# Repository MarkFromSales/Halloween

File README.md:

# Halloween
Various components associated with my Halloween decorations

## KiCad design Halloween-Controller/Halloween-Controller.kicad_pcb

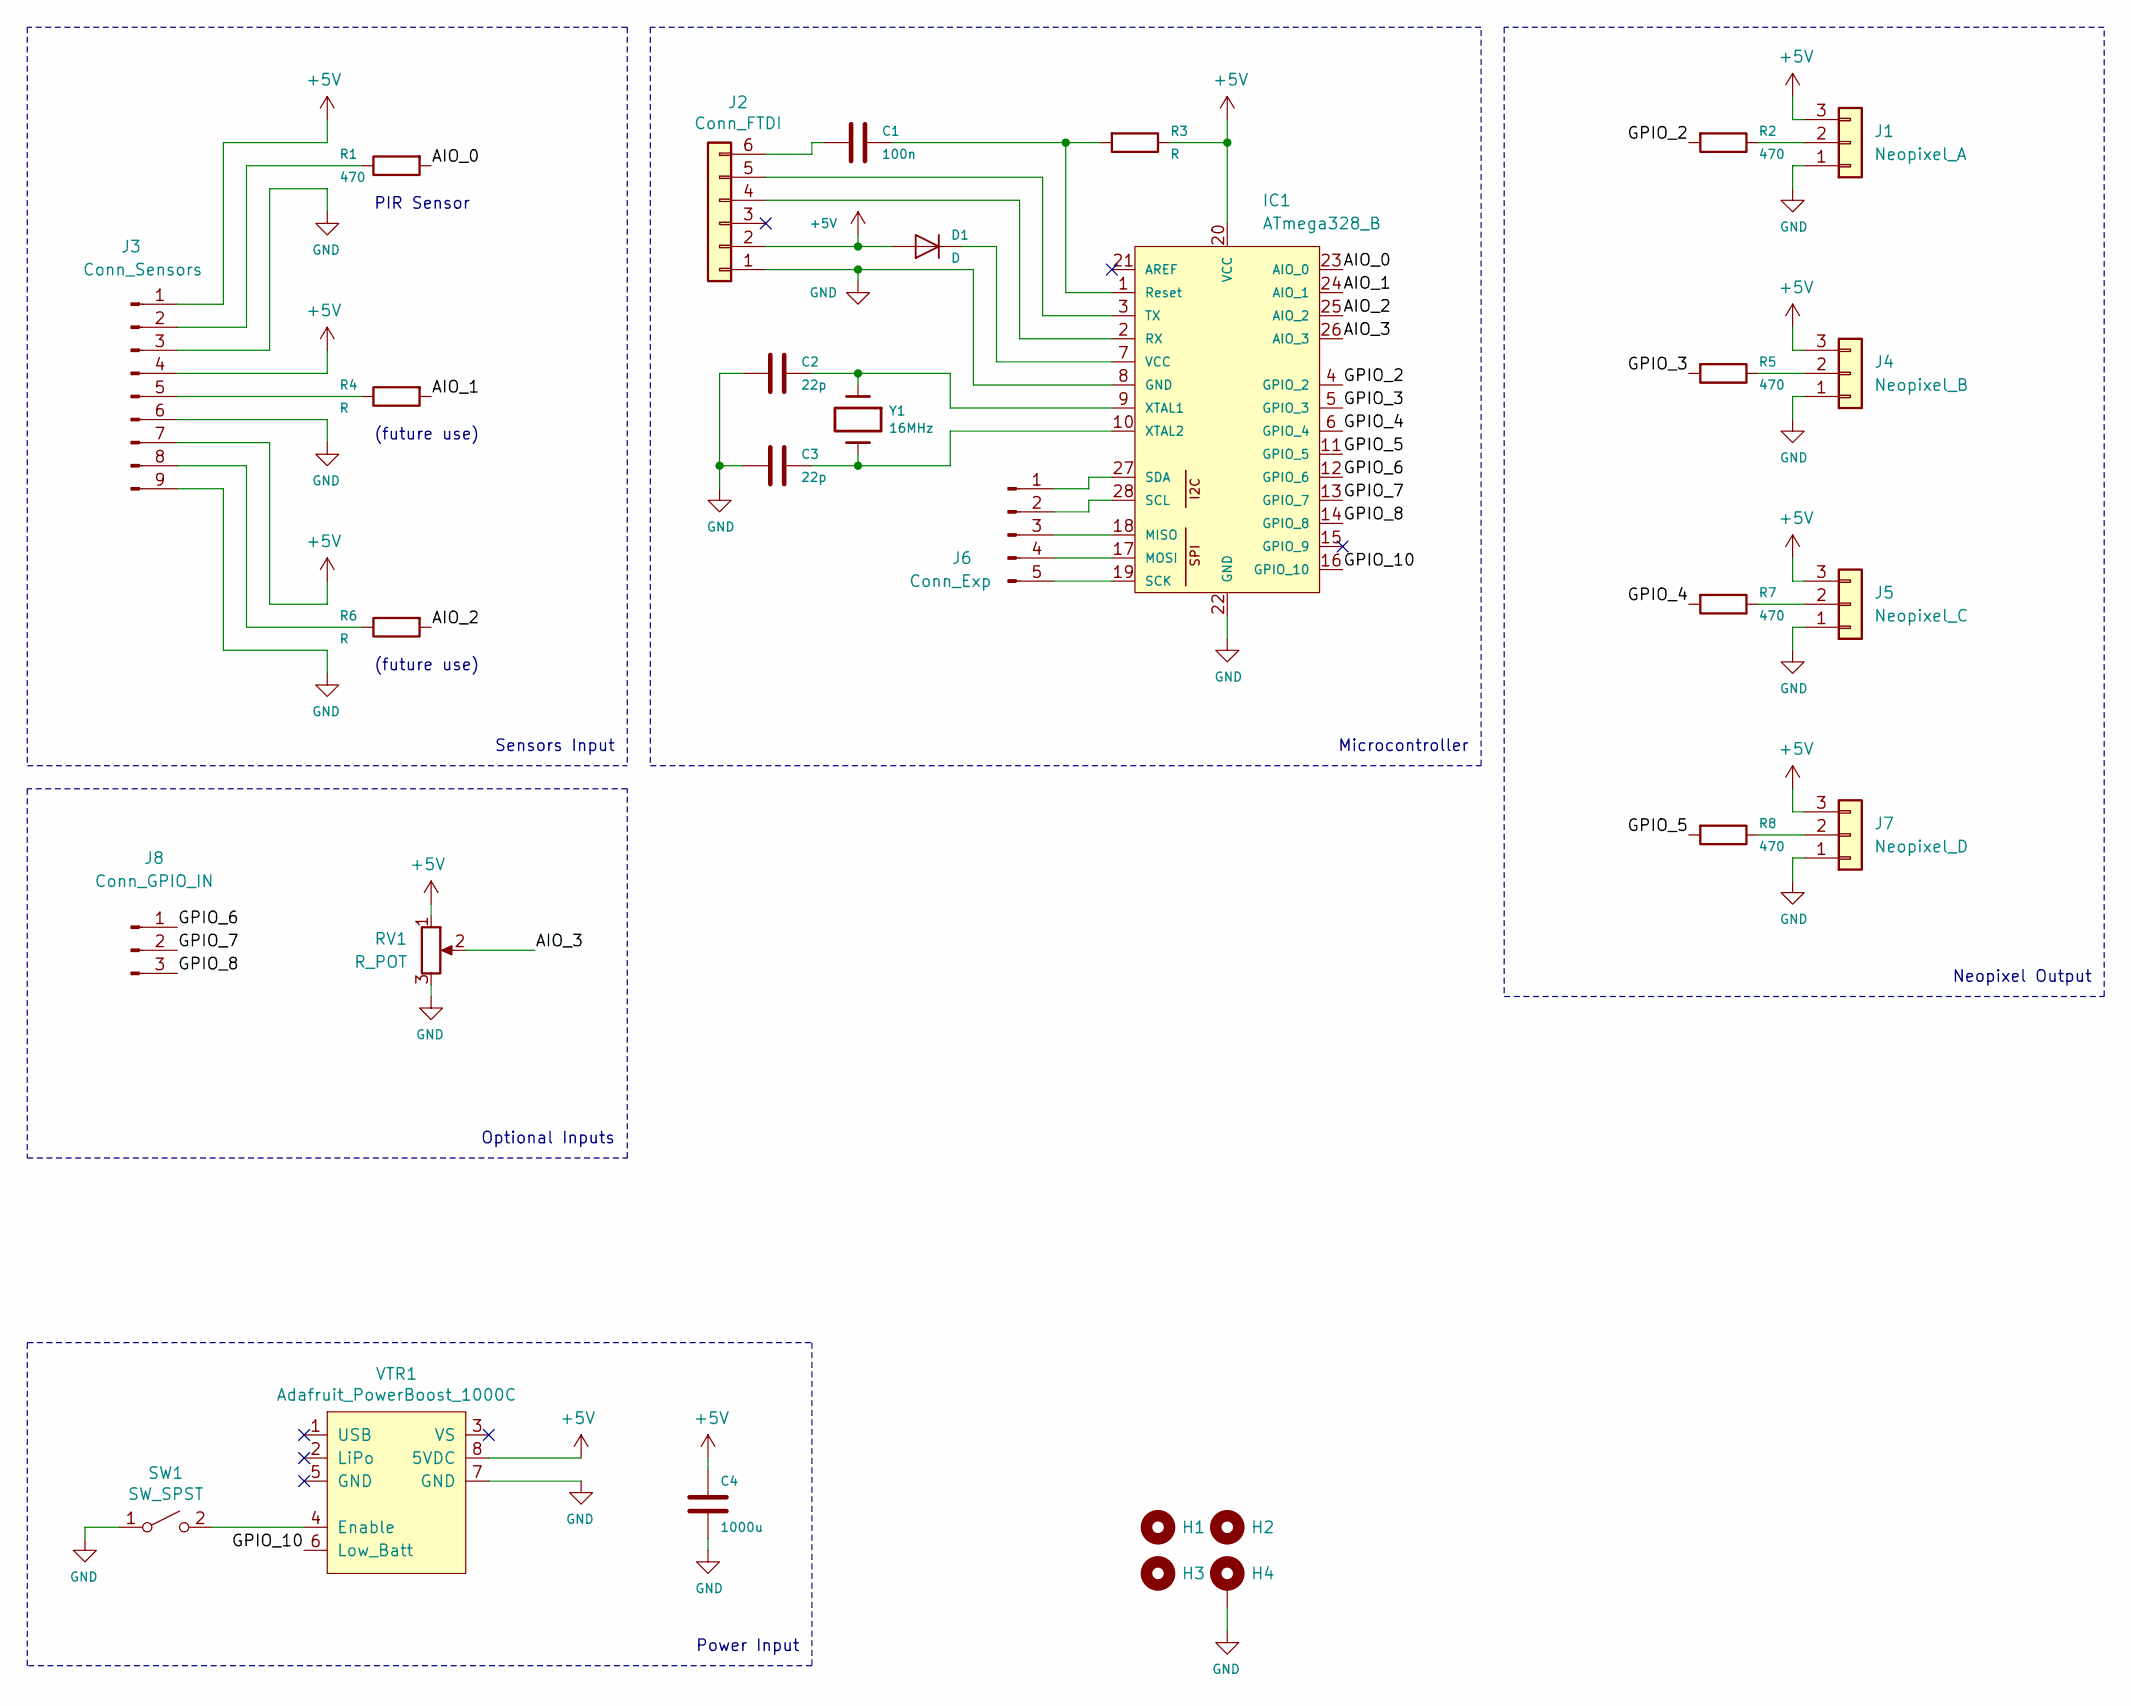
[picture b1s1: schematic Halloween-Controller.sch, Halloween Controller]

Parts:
C1: 100n; C_Disc_D10.5mm_W5.0mm_P7.50mm
C2, C3: 22p; C_0805_2012Metric_Pad1.15x1.40mm_HandSolder
C4: 1000u; C_1206_3216Metric_Pad1.42x1.75mm_HandSolder
D1: D; D_0805_2012Metric_Pad1.15x1.40mm_HandSolder
H1, H2, H3: MountingHole; MountingHole_3.2mm_M3
H4: MountingHole; MountingHole_3.2mm_M3_Pad
IC1: ATmega328_B; DIP-28_W7.62mm_Socket
J1: Neopixel_A; JST_XH_B03B-XH-A_1x03_P2.50mm_Vertical
J2: Conn_FTDI; PinHeader_1x06_P2.54mm_Vertical
J3: Conn_Sensors; PinHeader_1x09_P2.54mm_Vertical
J4: Neopixel_B; JST_XH_B03B-XH-A_1x03_P2.50mm_Vertical
J5: Neopixel_C; JST_XH_B03B-XH-A_1x03_P2.50mm_Vertical
J6: Conn_Exp; PinHeader_1x05_P2.54mm_Vertical
J7: Neopixel_D; JST_XH_B03B-XH-A_1x03_P2.50mm_Vertical
J8: Conn_GPIO_IN; PinHeader_1x03_P2.54mm_Vertical
R1, R2, R5, R7, R8: 470; R_0805_2012Metric
R3, R4, R6: R; R_0805_2012Metric
RV1: R_POT; Potentiometer
SW1: SW_SPST; PinHeader_1x02_P2.54mm_Vertical
VTR1: Adafruit_PowerBoost_1000C; PinHeader_1x08_P2.54mm_Vertical
Y1: 16MHz; Crystal_HC49-U_Vertical

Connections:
+5V: C4.1, D1.2 (A), IC1.20 (VCC), J1.3, J2.2, J3.1, J3.4, J3.7, J4.3, J5.3, J7.3, R3.1, RV1.1, VTR1.8 (5VDC)
/AIO_0: IC1.23 (AIO_0), R1.2
/AIO_1: IC1.24 (AIO_1), R4.2
/AIO_2: IC1.25 (AIO_2), R6.2
/AIO_3: IC1.26 (AIO_3), RV1.2
/GPIO_2: IC1.4 (GPIO_2), R2.2
/GPIO_3: IC1.5 (GPIO_3), R5.2
/GPIO_4: IC1.6 (GPIO_4), R7.2
/GPIO_5: IC1.11 (GPIO_5), R8.2
/GPIO_6: IC1.12 (GPIO_6), J8.1
/GPIO_7: IC1.13 (GPIO_7), J8.2
/GPIO_8: IC1.14 (GPIO_8), J8.3
/GPIO_10: IC1.16 (GPIO_10), VTR1.6 (Low_Batt)
GND: C2.2, C3.2, C4.2, H4.1, IC1.8 (GND), IC1.22 (GND), J1.1, J2.1, J3.3, J3.6, J3.9, J4.1, J5.1, J7.1, RV1.3, SW1.1 (A), VTR1.7 (GND)
unnamed: C1.1, IC1.1 (Reset), R3.2
unnamed: C1.2, J2.6
unnamed: C2.1, IC1.9 (XTAL1), Y1.1
unnamed: C3.1, IC1.10 (XTAL2), Y1.2
unnamed: D1.1 (K), IC1.7 (VCC)
unnamed: IC1.2 (RX), J2.4
unnamed: IC1.3 (TX), J2.5
unnamed: IC1.17 (MOSI), J6.4
unnamed: IC1.18 (MISO), J6.3
unnamed: IC1.19 (SCK), J6.5
unnamed: IC1.27 (SDA), J6.1
unnamed: IC1.28 (SCL), J6.2
unnamed: J1.2, R2.1
unnamed: J3.2, R1.1
unnamed: J3.5, R4.1
unnamed: J3.8, R6.1
unnamed: J4.2, R5.1
unnamed: J5.2, R7.1
unnamed: J7.2, R8.1
unnamed: SW1.2 (B), VTR1.4 (Enable)

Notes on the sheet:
PIR Sensor
(future use)
Sensors Input
Neopixel Output
Optional Inputs
Power Input
Microcontroller

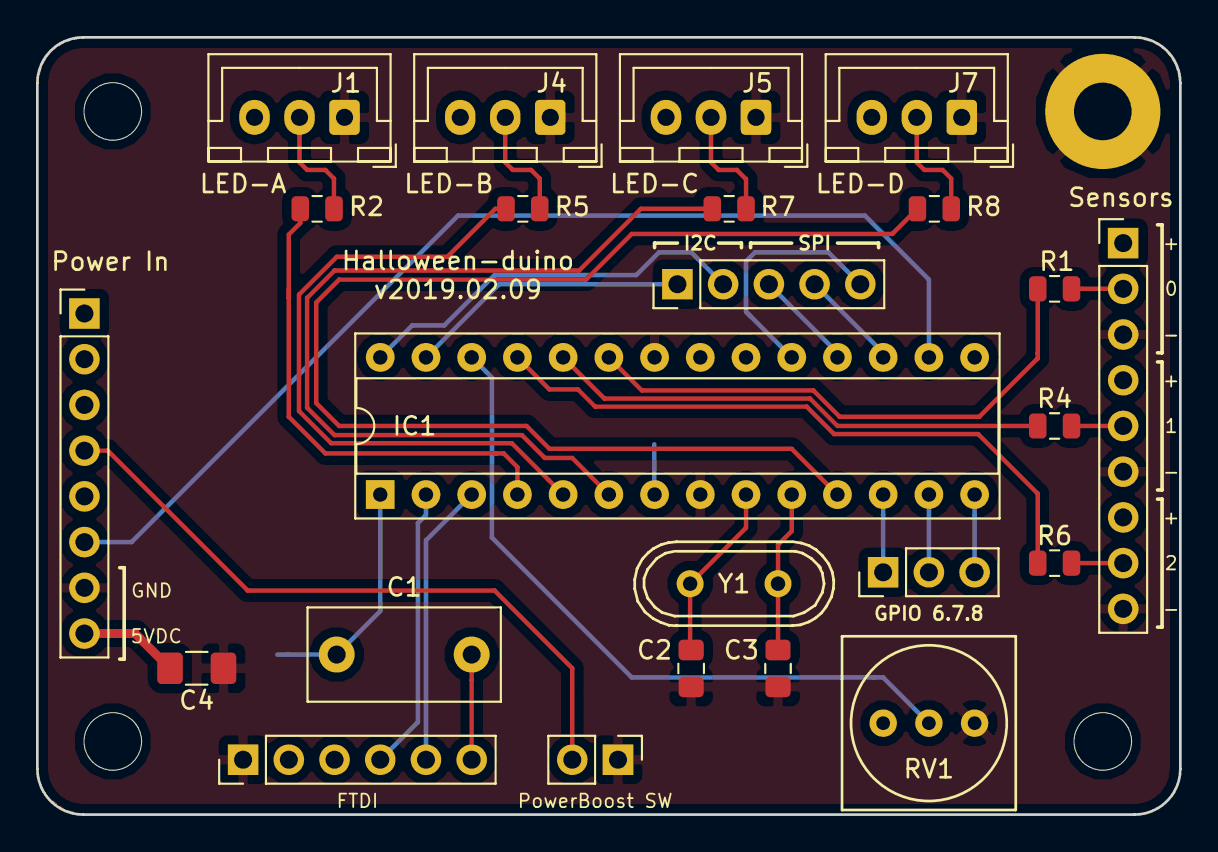
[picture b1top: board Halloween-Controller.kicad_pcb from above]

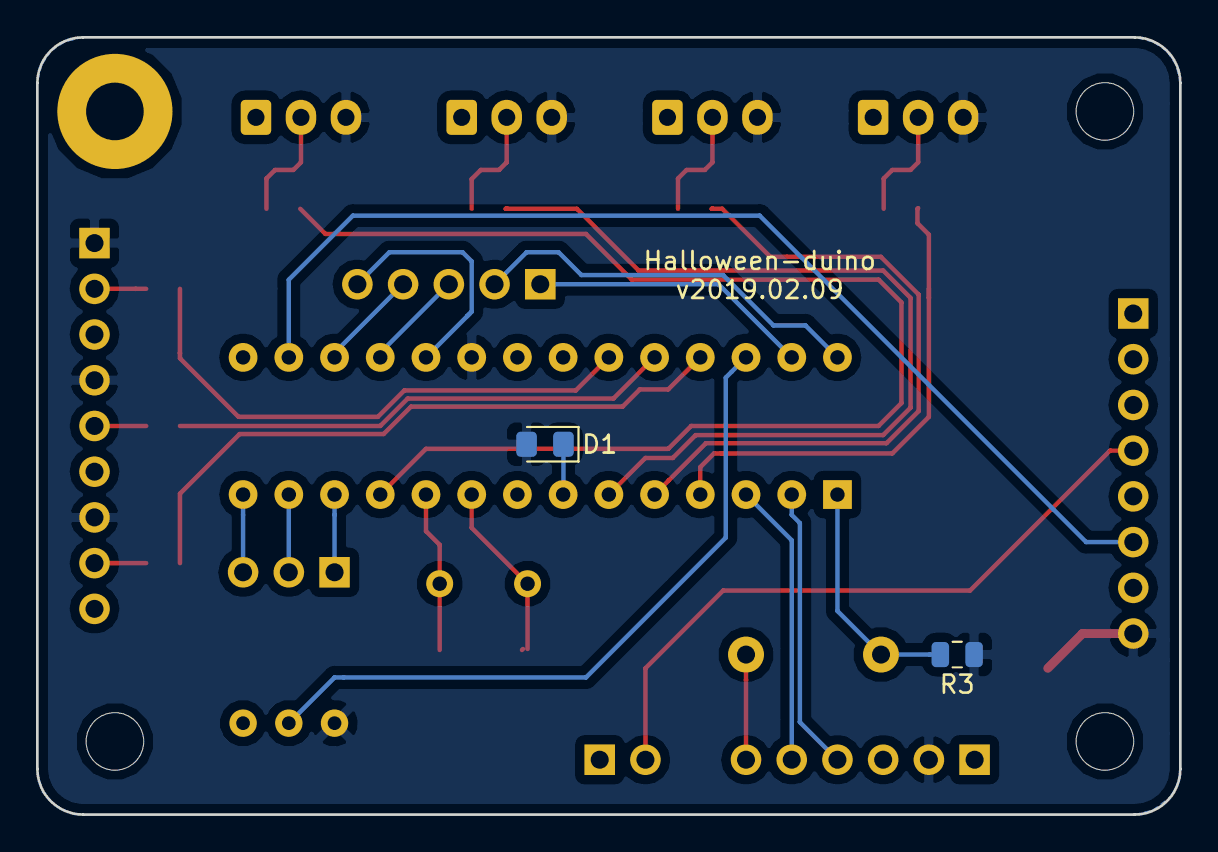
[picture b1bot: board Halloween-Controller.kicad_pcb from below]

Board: 2 copper layers, 63.5 x 43.2 mm, 30 parts (2 on the bottom side), 34 nets.

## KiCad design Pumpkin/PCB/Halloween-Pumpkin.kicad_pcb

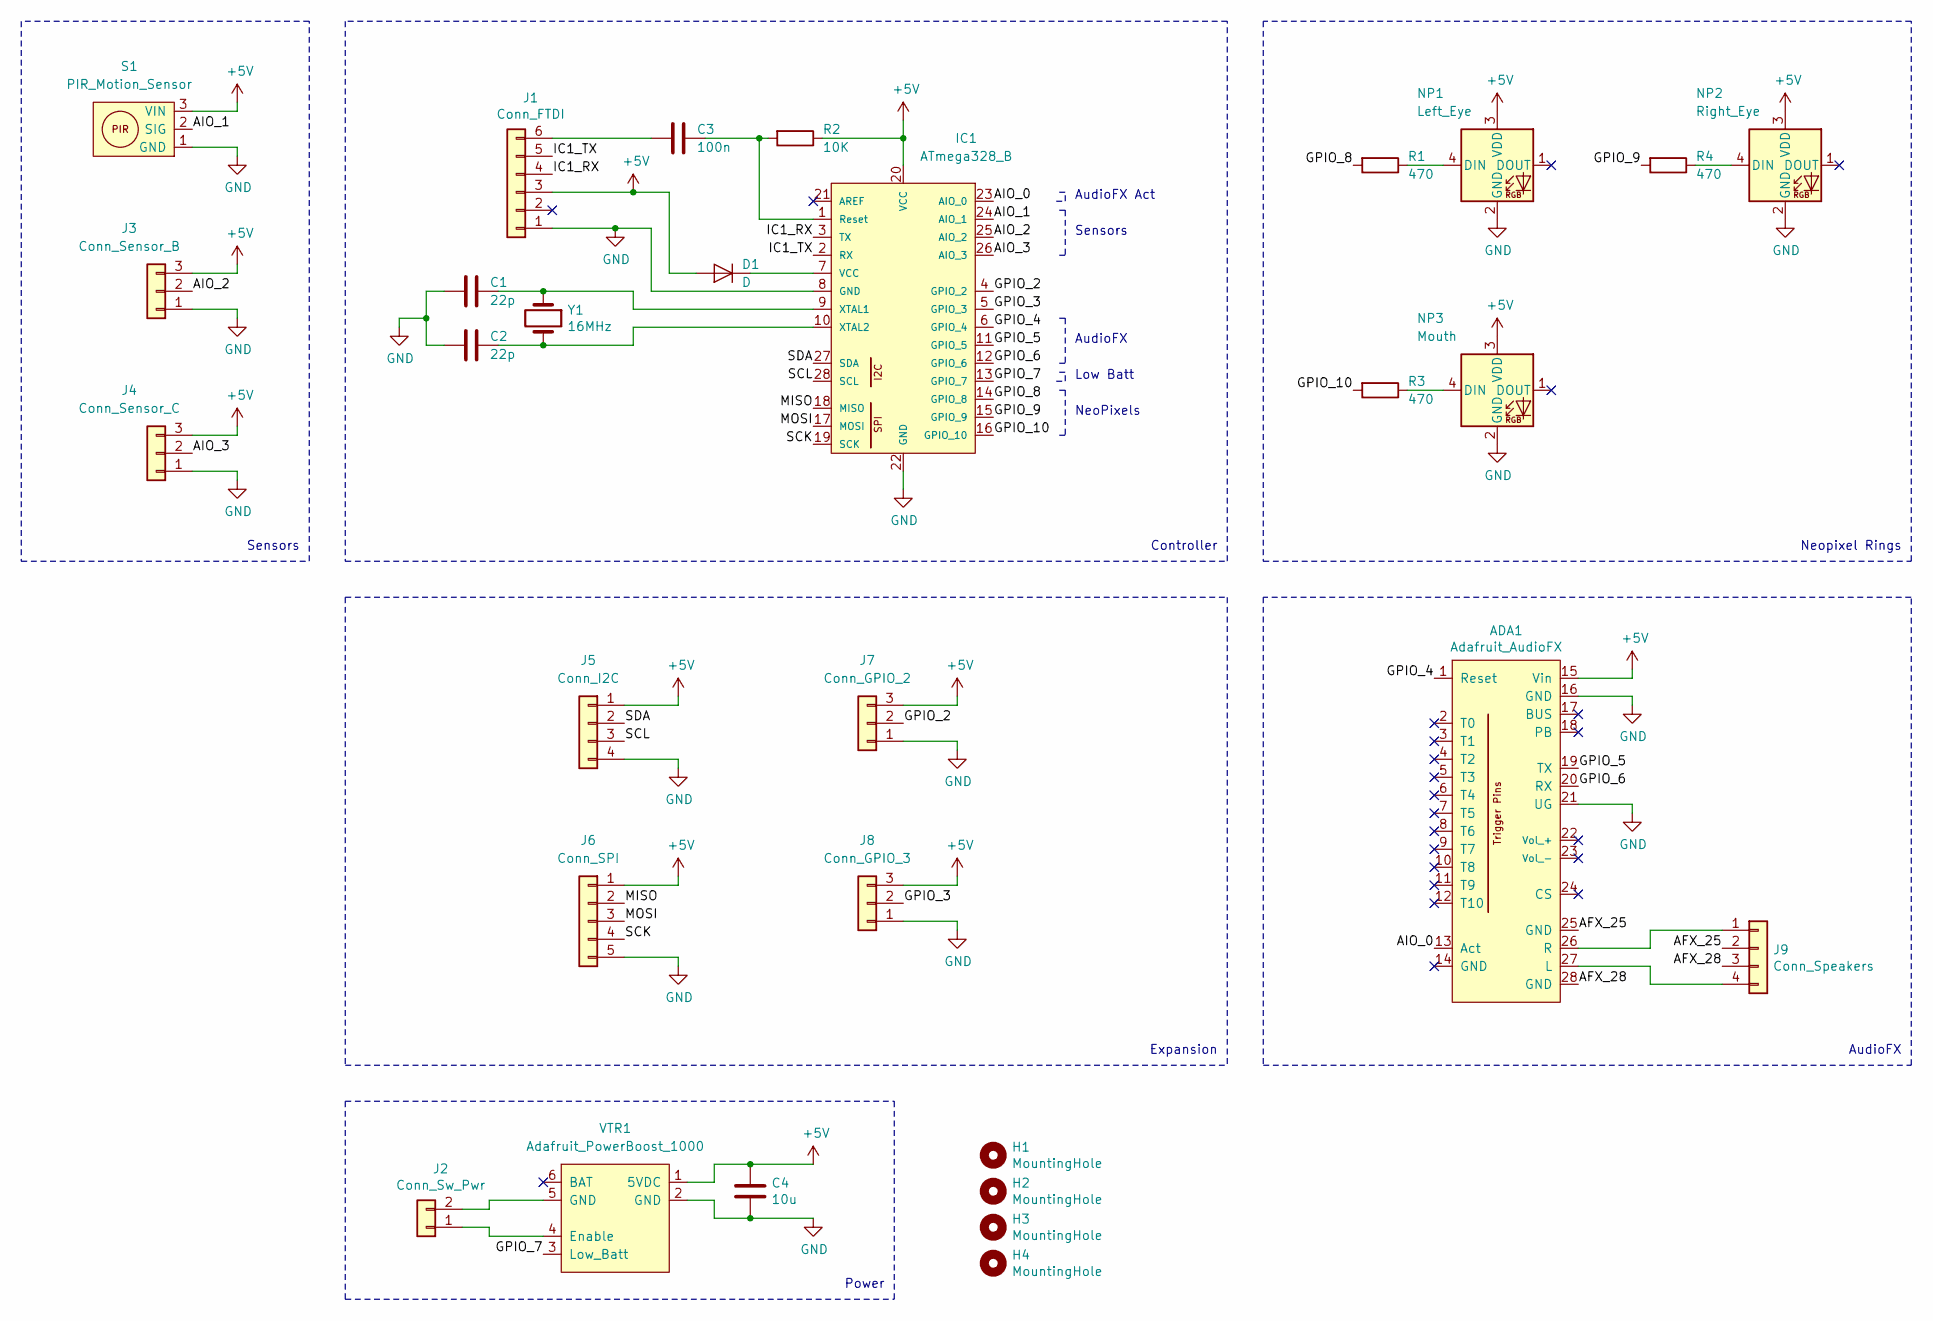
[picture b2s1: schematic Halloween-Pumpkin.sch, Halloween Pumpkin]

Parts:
ADA1: Adafruit_AudioFX; Adafruit AudioFX
C1, C2: 22p; C_1206_3216Metric_Pad1.42x1.75mm_HandSolder
C3: 100n; C_1206_3216Metric_Pad1.42x1.75mm_HandSolder
C4: 10u; C_1206_3216Metric_Pad1.42x1.75mm_HandSolder
D1: D; D_1206_3216Metric_Pad1.42x1.75mm_HandSolder
H1, H2, H3, H4: MountingHole; MountingHole_3.2mm_M3
IC1: ATmega328_B; DIP-28_W7.62mm_Socket
J1: Conn_FTDI; PinHeader_1x06_P2.54mm_Vertical
J2: Conn_Sw_Pwr; PinHeader_1x02_P2.54mm_Vertical
J3: Conn_Sensor_B; PinHeader_1x03_P2.54mm_Vertical
J4: Conn_Sensor_C; PinHeader_1x03_P2.54mm_Vertical
J5: Conn_I2C; PinHeader_1x04_P2.54mm_Vertical
J6: Conn_SPI; PinHeader_1x05_P2.54mm_Vertical
J7: Conn_GPIO_2; PinHeader_1x03_P2.54mm_Vertical
J8: Conn_GPIO_3; PinHeader_1x03_P2.54mm_Vertical
J9: Conn_Speakers; JST_PH_B4B-PH-K_1x04_P2.00mm_Vertical
NP1: Left_Eye; PinHeader_1x04_P2.54mm_Vertical
NP2: Right_Eye; PinHeader_1x04_P2.54mm_Vertical
NP3: Mouth; PinHeader_1x04_P2.54mm_Vertical
R1, R3, R4: 470; R_1206_3216Metric_Pad1.42x1.75mm_HandSolder
R2: 10K; R_1206_3216Metric_Pad1.42x1.75mm_HandSolder
S1: PIR_Motion_Sensor; PinHeader_1x03_P2.54mm_Vertical
VTR1: Adafruit_PowerBoost_1000; PinHeader_1x06_P2.54mm_Vertical
Y1: 16MHz; Crystal_HC49-U_Vertical

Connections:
+5V: ADA1.15 (Vin), C4.1, D1.2 (A), IC1.20 (VCC), J1.3, J3.3, J4.3, J5.1, J6.1, J7.3, J8.3, NP1.3 (VDD), NP2.3 (VDD), NP3.3 (VDD), R2.1, S1.3 (VIN), VTR1.1 (5VDC)
/AFX_25: ADA1.25 (GND), J9.2
/AFX_28: ADA1.28 (GND), J9.3
/AIO_0: ADA1.13 (Act), IC1.23 (AIO_0)
/AIO_1: IC1.24 (AIO_1), S1.2 (SIG)
/AIO_2: IC1.25 (AIO_2), J3.2
/AIO_3: IC1.26 (AIO_3), J4.2
/GPIO_2: IC1.4 (GPIO_2), J7.2
/GPIO_3: IC1.5 (GPIO_3), J8.2
/GPIO_4: ADA1.1 (Reset), IC1.6 (GPIO_4)
/GPIO_5: ADA1.19 (TX), IC1.11 (GPIO_5)
/GPIO_6: ADA1.20 (RX), IC1.12 (GPIO_6)
/GPIO_7: IC1.13 (GPIO_7), VTR1.3 (Low_Batt)
/GPIO_8: IC1.14 (GPIO_8), R1.2
/GPIO_9: IC1.15 (GPIO_9), R4.2
/GPIO_10: IC1.16 (GPIO_10), R3.2
/IC1_RX: IC1.3 (TX), J1.4
/IC1_TX: IC1.2 (RX), J1.5
/MISO: IC1.18 (MISO), J6.2
/MOSI: IC1.17 (MOSI), J6.3
/SCK: IC1.19 (SCK), J6.4
/SCL: IC1.28 (SCL), J5.3
/SDA: IC1.27 (SDA), J5.2
GND: ADA1.16 (GND), ADA1.21 (UG), C1.2, C2.2, C4.2, IC1.8 (GND), IC1.22 (GND), J1.1, J3.1, J4.1, J5.4, J6.5, J7.1, J8.1, NP1.2 (GND), NP2.2 (GND), NP3.2 (GND), S1.1 (GND), VTR1.2 (GND)
unnamed: ADA1.26 (R), J9.1
unnamed: ADA1.27 (L), J9.4
unnamed: C1.1, IC1.9 (XTAL1), Y1.1
unnamed: C2.1, IC1.10 (XTAL2), Y1.2
unnamed: C3.1, IC1.1 (Reset), R2.2
unnamed: C3.2, J1.6
unnamed: D1.1 (K), IC1.7 (VCC)
unnamed: J2.1, VTR1.4 (Enable)
unnamed: J2.2, VTR1.5 (GND)
unnamed: NP1.4 (DIN), R1.1
unnamed: NP2.4 (DIN), R4.1
unnamed: NP3.4 (DIN), R3.1

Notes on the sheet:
AudioFX
Low Batt
NeoPixels
Sensors
AudioFX Act
Controller
Neopixel Rings
Expansion
Power

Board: 2 copper layers, 30 parts (0 on the bottom side), 36 nets, no tracks yet.

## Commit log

2019-02-10 Continued work, not yet breadboard tested
2019-02-13 Updated structure
2019-03-20 WIP....
